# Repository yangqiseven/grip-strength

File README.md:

# grip-strength

## Introduction

This program interfaces with the Phidgets [CZL301C](http://www.phidgets.com/products.php?product_id=3138) load cell. It graphically displays the force value (in kg) which is acting on the load cell. It is designed to operate on a Raspberry Pi.

It was originally envisioned to work as a grip strength measuring device. However, it could be re-purposed for other uses.

The load cell has an internal wheatstone bridge. Its output voltage varies linearly with the force applied on the load cell. It works when the load cell is compressed ("pushed") and when it is contracted ("pulled"). The current implementation only works during compression. The output voltage of the load cell is then amplified with the [AD623](http://docs-europe.electrocomponents.com/webdocs/10d9/0900766b810d9003.pdf) amplifier. This amplified voltage is fed to the [AD7705](http://docs-europe.electrocomponents.com/webdocs/077f/0900766b8077ff32.pdf) ADC. The output values of the ADC connects to the Raspberry Pi via SPI.

The program uses QT4 to graphically plot the data.

## Hardware setup

There is a pre-routed PCB file located at:

```
hardware/grip_strength_board.brd
```

It is relatively simple to fabricate. There is more information about the hardware design in the project wiki.

Once fabricated the PCB mounts directly on the GPIO pins such that the last row of the PCB header is on the 13th row of the GPIO pins.

## Installation & Usage

### Pre-requisites & Dependencies

You must have the following libraries and frameworks installed:

1. [BCM2835](http://www.airspayce.com/mikem/bcm2835/)
2. [QT4.8](http://doc.qt.io/qt-4.8/installation.html)

The Raspberry Pi must have [SPI](https://www.raspberrypi.org/documentation/hardware/raspberrypi/spi/README.md) enabled. The most straight forward method of enabling SPI is using [raspi-config](https://www.raspberrypi.org/documentation/configuration/raspi-config.md):

```
sudo raspi-config
```

In addition, you need to have an X server such as [Xorg](https://www.x.org/wiki/) running for `startx` to display the graphical output.

### Download

To download this program, use `git clone`:

```
git clone https://github.com/michaelorr92/grip-strength
```

### Compiling & Running

To compile the program use `qmake` (from the root directory), which generates a makefile, you can then run `make` to compile an output program file.

```
qmake
make
```

To run the program:

```
startx ./build/grip-strength
```

## Testing

As it is difficult to test both the GUI thread and the thread which reads from the ADC (as it needs to interface with physical hardware) the project currently only tests the ring buffer (which is used to store data between the two threads) implementation. The file `test.c` is used to check assumptions using assert.

To complie:

```
gcc -std=c99 -o test/buffer test/test.c  src/ringBuffer.c
```

To run:

```
./test/buffer
```

## Acknowledgements

The source code in this project which is used for interacting with the SPI is originally from [rpi_AD7705_test_software](https://github.com/berndporr/rpi_AD7705_test_software).

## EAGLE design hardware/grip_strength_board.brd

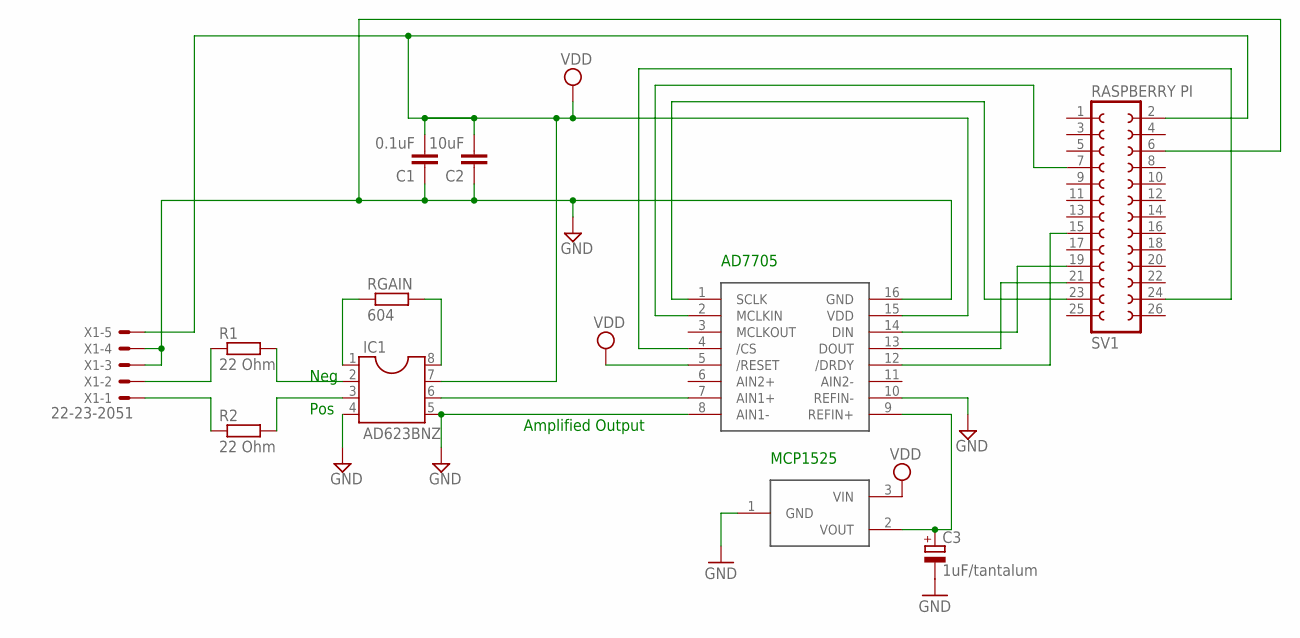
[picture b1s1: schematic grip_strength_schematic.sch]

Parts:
C1: 0.1uF; C5B2.5
C2: 10uF; C5B2.5
C3: 1uF/tantalum; TT2D7
IC1: AD623BNZ; SOCKET-08
R1, R2: 22 Ohm; 0207/10
RGAIN: 604; 0207/10
SV1: RASPBERRY PI; FE13-2
U$1: AD7705; DIP16
U$2: MCP1525; TO92
X1: 22-23-2051

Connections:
GND: C1.1, C2.1, C3.-, IC1.4, IC1.5, SV1.6, U$1.8 (AIN1-), U$1.10 (REFIN-), U$1.16 (GND), U$2.1 (GND), X1.3, X1.4
unnamed: IC1.1, RGAIN.1
unnamed: IC1.8, RGAIN.2
unnamed: R1.1, X1.2
unnamed: IC1.2, R1.2
unnamed: IC1.6, U$1.7 (AIN1+)
unnamed: SV1.23, U$1.1 (SCLK)
unnamed: SV1.7, U$1.2 (MCLKIN)
unnamed: SV1.24, U$1.4 (/CS)
unnamed: SV1.19, U$1.14 (DIN)
unnamed: SV1.21, U$1.13 (DOUT)
unnamed: SV1.15, U$1.12 (/DRDY)
unnamed: C3.+, U$1.9 (REFIN+), U$2.2 (VOUT)
unnamed: R2.1, X1.1
unnamed: IC1.3, R2.2
VDD: C1.2, C2.2, IC1.7, SV1.2, U$1.5 (/RESET), U$1.15 (VDD), U$2.3 (VIN), X1.5

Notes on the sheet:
Amplified Output
Pos
Neg
MCP1525
AD7705

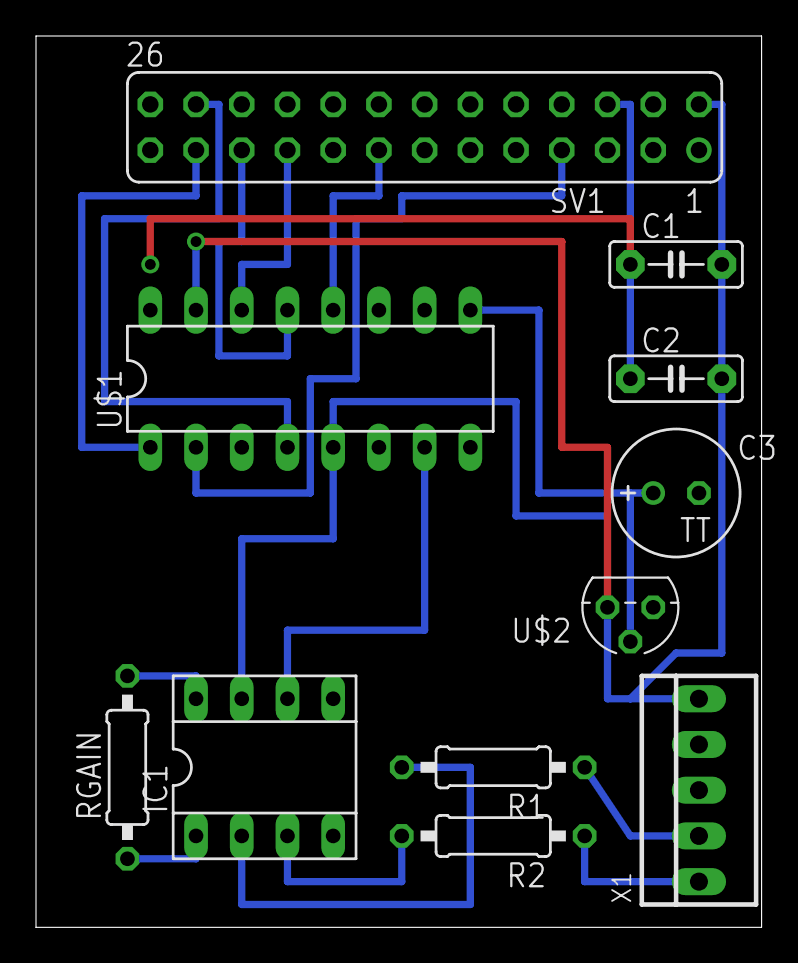
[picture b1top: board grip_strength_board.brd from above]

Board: 2 copper layers, 40.3 x 49.5 mm, 11 parts (0 on the bottom side), 16 nets.

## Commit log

2017-03-19 Added makefile
2017-03-19 Added QWT project files
2017-03-19 Added skeleton adc reader code
2017-03-19 Added adc reader header
2017-03-19 Added basic window file
2017-03-19 Added window file header
2017-03-19 Added main qt file
2017-03-19 Added a gitignore
2017-03-19 Removed makefile
2017-03-19 Renamed internal project name
2017-03-19 Changed file permissions
2017-03-19 Updated gitignore
2017-03-19 Fixed typo
2017-03-19 Removed knob and thermometer
2017-03-19 Added a second plot which is for "female" data, the original plot is for "male" data
2017-03-19 Added qcustom plot library
2017-03-19 Changed code to utilise qcustomplot library, scrapped the second plot Going to display all data on one graph
2017-03-22 Fixed path of library
2017-03-22 Updated graph title
2017-03-26 Added ring buffer code
2017-03-26 Added code for testing ring buffer implementation
2017-03-26 Linked ringBuffer to rest of program
2017-03-26 Added linkage to work with C++
2017-03-26 Changed types of some variables to unit8_t
2017-03-26 Added adc thread
2017-03-27 Added some global variables for testing
2017-03-27 Moved ring buffer initialisation to main
2017-03-27 Added new files to be compiled
2017-03-27 Added some dummy data for testing
2017-03-27 Passed ringBuffer in a more OOP manner by utilising the constructor
2017-03-27 Passed mutex from main to adc via constructor
2017-03-27 Removed global variables
2017-03-27 Renamed some member functions to be more intuitive
2017-03-27 Passed references to mutex and ring_buffer via constructor
2017-03-27 Added graph label
2017-03-27 Set window size to be full screen
2017-03-27 Faked some data for testing
2017-03-27 Added code to read from ring buffer and plot
2017-03-27 Changed screen reading adc rate to 1 ms
2017-03-27 Removed logging code
2017-03-27 Removed unused variable
2017-03-27 Added legend with real time data
2017-03-27 Moved max to constructor
2017-03-28 Added code to interact with ADC
2017-03-28 Reads from ADC via SPI and writes to ring buffer
2017-04-05 Removed comments
2017-04-05 Moved SPI code into ADC reader file
2017-04-05 Fixed library issues
2017-04-05 Fixed sampling rate
2017-04-05 Updated refresh rate to be around 66 Hz
2017-04-05 ADC samples as fast as possible
2017-04-05 Changed sizes from uint8 to uint16
2017-04-05 Added code to convert from raw adc numbers to kg
2017-04-06 Tidied some comments
2017-04-06 Beautified code
2017-04-06 Set refresh rate to be around 60 Hz
2017-04-06 Updated test code to use 16 bit ints
2017-04-06 Moved test code to test folder
2017-04-06 Tidied project folder structure
2017-04-06 Fixed path
2017-04-06 Fixed path of build directory
2017-04-06 Changed displayed value to floating point
2017-04-06 Added authors to license
2017-04-14 Calibrated conversion
2017-04-14 Added PCB files
